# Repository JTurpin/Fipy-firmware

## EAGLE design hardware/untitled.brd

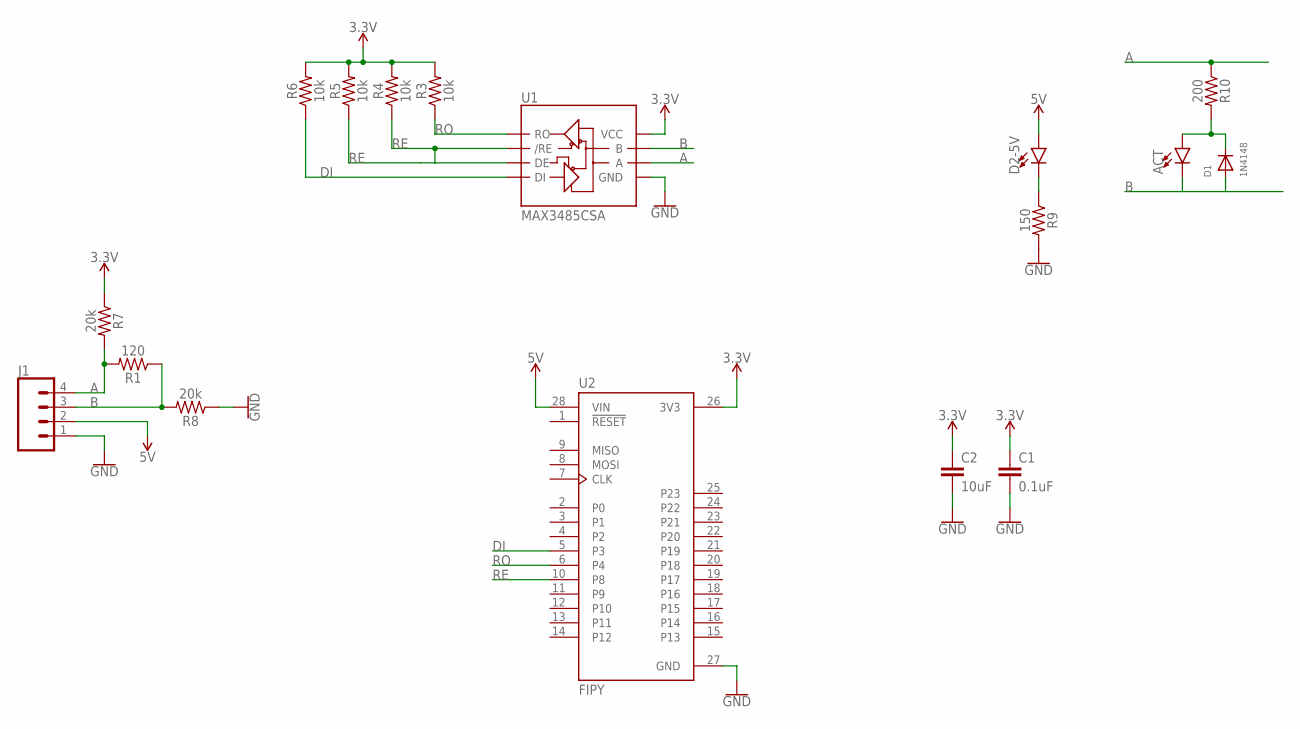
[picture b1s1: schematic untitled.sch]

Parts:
ACT: LED0603; LED-0603
C1: 0.1uF; 0603
C2: 10uF; 0603
D1: 1N4148; SOD-123
D2-5V: LED0603; LED-0603
J1: CONN_04LOCK_LONGPADS; 1X04_LOCK_LONGPADS
R1: 120; 0805
R3, R4, R5, R6: 10k; 0603
R7, R8: 20k; 0805
R9: 150; 0805
R10: 200; 0805
U1: MAX3485CSA; SO08
U2: FIPY; MODULE_FIPY

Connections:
3.3V: C1.1, C2.1, R3.2, R4.2, R5.2, R6.2, R7.1, U1.8 (VCC), U2.26 (3V3)
5V: D2-5V.A, J1.2, U2.28 (VIN)
A: J1.4, R1.2, R7.2, R10.1, U1.6 (A)
B: ACT.C, D1.A, J1.3, R1.1, R8.2, U1.7 (B)
DI: R6.1, U1.4 (DI), U2.5 (P3)
GND: C1.2, C2.2, J1.1, R8.1, R9.2, U1.5 (GND), U2.27 (GND)
unnamed: D2-5V.C, R9.1
unnamed: ACT.A, D1.C, R10.2
RE: R4.1, R5.1, U1.2 (/RE), U1.3 (DE), U2.10 (P8)
RO: R3.1, U1.1 (RO), U2.6 (P4)

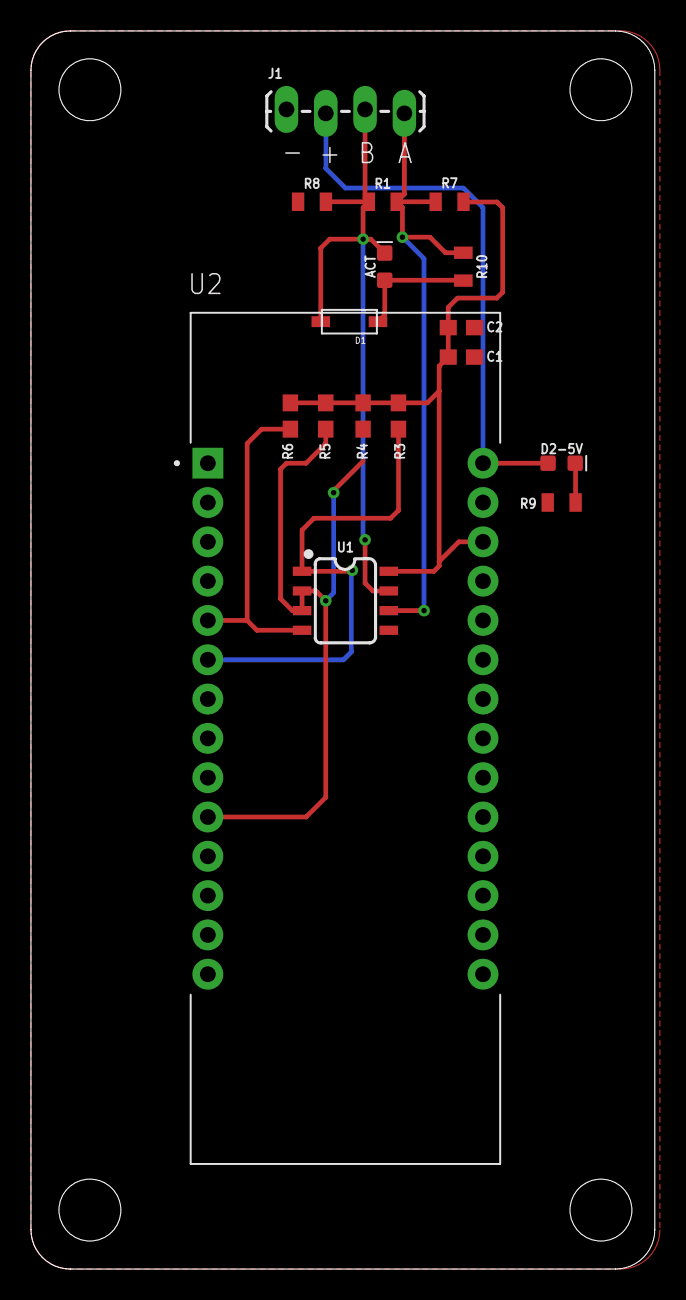
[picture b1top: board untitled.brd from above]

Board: 2 copper layers, 40.3 x 80.0 mm, 17 parts (0 on the bottom side), 10 nets.

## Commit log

2022-10-01 adding sunspec submodule

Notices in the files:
parts and their libraries:
SparkFun-Capacitors: Licensing: Creative Commons ShareAlike 4.0 International - https://creativecommons.org/licenses/by-sa/4.0
